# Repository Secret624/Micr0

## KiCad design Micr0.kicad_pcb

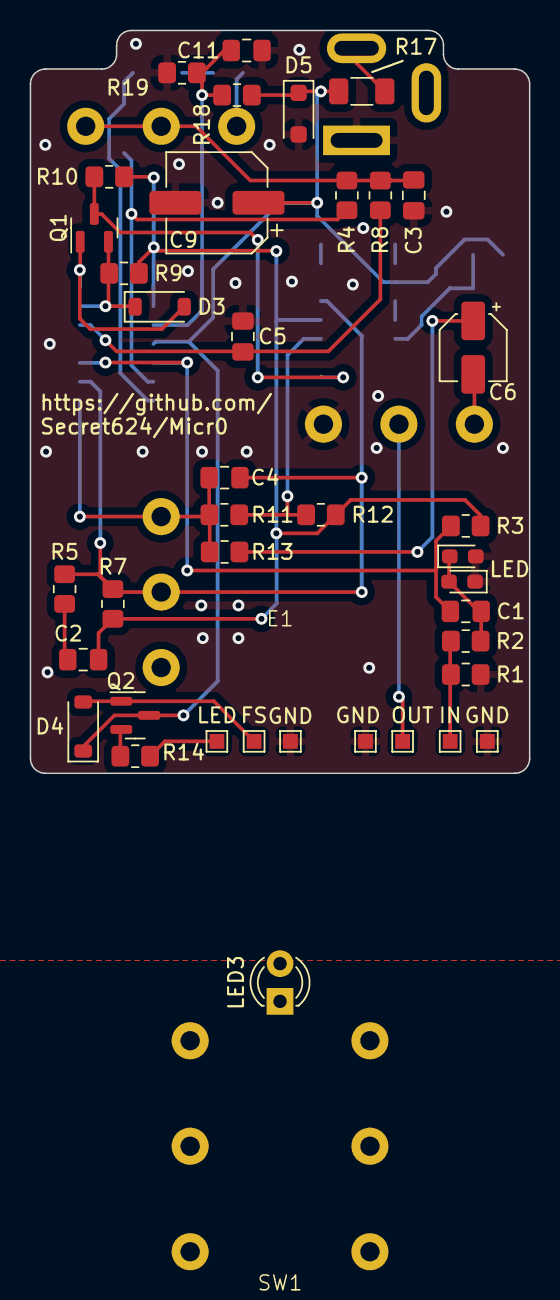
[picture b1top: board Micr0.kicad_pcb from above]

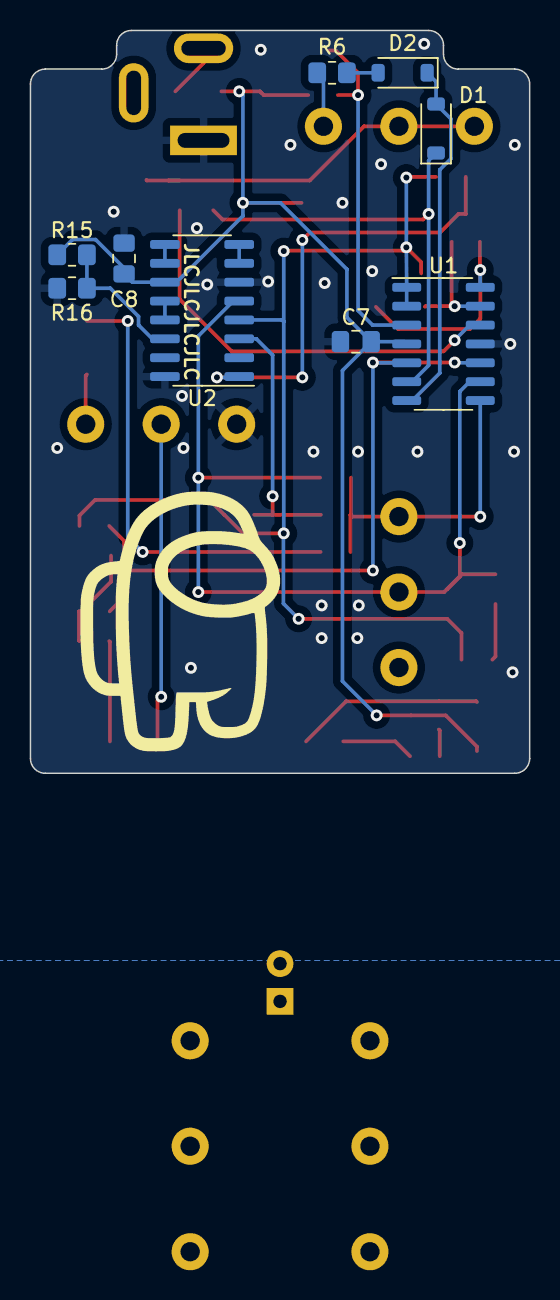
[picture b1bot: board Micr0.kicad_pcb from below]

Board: 2 copper layers, 33.6 x 50.0 mm, 56 parts (12 on the bottom side), 32 nets.

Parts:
C1, C7, C8: 10nF; C_0805_2012Metric_Pad1.18x1.45mm_HandSolder
C2: 4.7nF; C_0805_2012Metric_Pad1.18x1.45mm_HandSolder
C3, C5, C11: 1uF; C_0805_2012Metric_Pad1.18x1.45mm_HandSolder
C4: 100pF; C_0805_2012Metric_Pad1.18x1.45mm_HandSolder
C6: 10uF; CP_Elec_4x5.4
C9: 100uF; CP_Elec_6.3x5.4
D1, D2, D3, D4: 1N4148W; D_SOD-123
D5: 1N4001; D_SOD-123F
E1: 1590B
J1, J2: AudioJack2; PJ-612
J3: Barrel_Jack_Switch; BarrelJack_Kycon_KLDX-0202-xC_Horizontal
LED1, LED2: LED_Small; LED_0603_1608Metric_Pad1.05x0.95mm_HandSolder
LED3: LED_Small; LED_D3.0mm
Q1: BC807; SOT-23
Q2: MMBF170; SOT-23
R1, R3, R10, R18, R19: 1M; R_0805_2012Metric_Pad1.20x1.40mm_HandSolder
R2, R8, R9, R13: 1k; R_0805_2012Metric_Pad1.20x1.40mm_HandSolder
R4: 470k; R_0805_2012Metric_Pad1.20x1.40mm_HandSolder
R5, R7, R11, R15, R16: 10k; R_0805_2012Metric_Pad1.20x1.40mm_HandSolder
R6: 100Ω; R_0805_2012Metric_Pad1.20x1.40mm_HandSolder
R12: 220Ω; R_0805_2012Metric_Pad1.20x1.40mm_HandSolder
R14: 4.7k; R_0805_2012Metric_Pad1.20x1.40mm_HandSolder
R17: 39Ω; R_1206_3216Metric_Pad1.30x1.75mm_HandSolder
RV1, RV2, RV3: R_Potentiometer; UT right angle long pin
SW1: SW_DPDT_x2; Ural dpdt
TP1: OUT; TestPoint_Pad_1.0x1.0mm
TP2, TP5, TP7: GND; TestPoint_Pad_1.0x1.0mm
TP3: IN; TestPoint_Pad_1.0x1.0mm
TP4: FS; TestPoint_Pad_1.0x1.0mm
TP6: LED; TestPoint_Pad_1.0x1.0mm
U1: TL074; SO-14_3.9x8.65mm_P1.27mm
U2: LM13700; SOP-16_3.9x9.9mm_P1.27mm

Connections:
+5V: C2.2, R3.1, R7.1, R9.1, R10.1, R12.1, U1.1, U1.2 (-), U2.4 (-)
+9V: C7.1, C8.1, C9.1, D4.1 (K), D5.1 (K), Q2.3 (D), R15.1, R17.2, R18.1, U1.4 (V+), U2.11 (V+)
FS_engi: D4.2 (A), Q2.1 (G), SW1.4 (A), TP4.1
GND: C3.2, C5.2, C7.2, C8.2, C9.2, C11.1, D5.2 (A), J3.1, LED1.2 (A), LED2.1 (K), LED3.1 (K), R1.2, R16.2, R19.2, RV1.1, TP2.1, TP5.1, TP7.1, U1.11 (V-), U2.6 (V-), U2.16
IN_engi_pcb: R1.1, R2.1, SW1.1 (A), TP3.1
unnamed: C2.1, R5.1
unnamed: C3.1, R4.1, R8.1, RV2.2, RV2.3
unnamed: C4.1, R11.2, R13.1, RV3.1, U1.8
unnamed: C6.1, R13.2
unnamed: C6.2, RV1.3
unnamed: D1.2 (A), D2.1 (K), U1.7
unnamed: D1.1 (K), R4.2, U1.6 (-)
unnamed: D2.2 (A), R6.1
unnamed: D3.2 (A), Q1.1 (B), U1.14
unnamed: D3.1 (K), Q1.2 (E), R9.2, U1.13 (-)
unnamed: J3.2, R17.1
unnamed: C1.2, LED1.1 (K), LED2.2 (A), R2.2
unnamed: LED3.2 (A), R14.2, TP6.1
unnamed: Q1.3 (C), R10.2, U2.1
unnamed: Q2.2 (S), R14.1
unnamed: R6.2, RV2.1
unnamed: C11.2, R18.2, R19.1, U1.3 (+)
unnamed: C1.1, R3.2, U1.5 (+), U1.10 (+)
unnamed: C4.2, R5.2, R7.2, RV3.2, U1.9 (-), U2.5
unnamed: C5.1, R8.2, U1.12 (+)
unnamed: U2.7, U2.8
unnamed: U2.9, U2.10
unnamed: R15.2, R16.1, U2.14 (+)
unnamed: U2.12, U2.13 (-)
unnamed: R11.1, R12.2, U2.3 (+)
OUT_engi: SW1.3 (C), SW1.6 (C)
OUT_engi_pcb: RV1.2, SW1.5 (B), TP1.1

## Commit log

2023-11-18 Added gerbers
